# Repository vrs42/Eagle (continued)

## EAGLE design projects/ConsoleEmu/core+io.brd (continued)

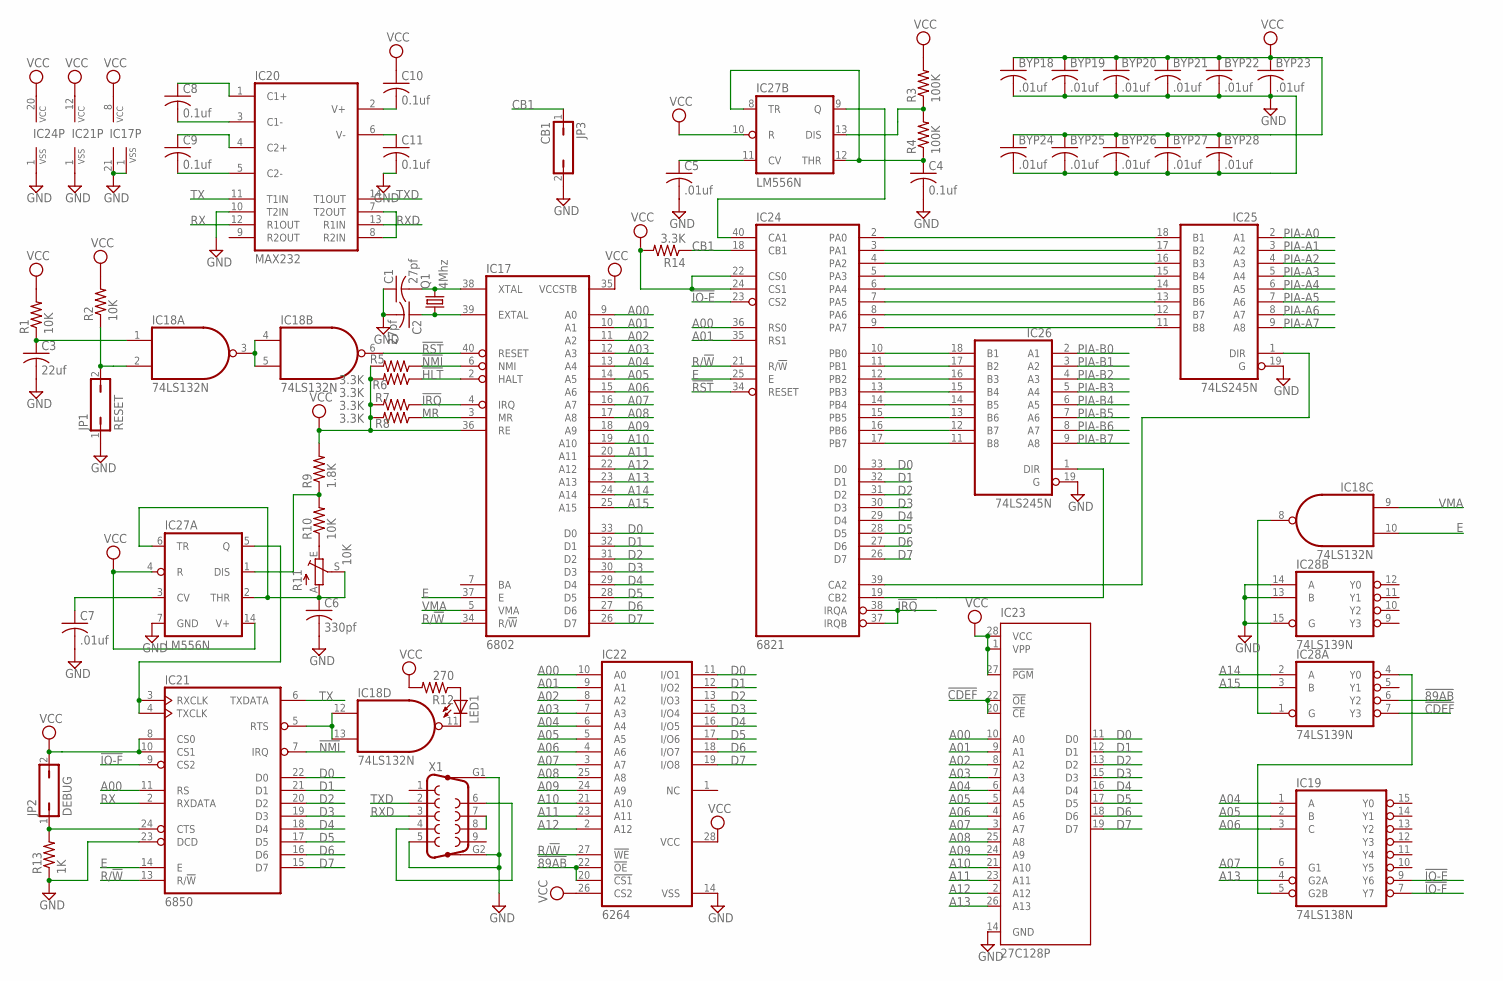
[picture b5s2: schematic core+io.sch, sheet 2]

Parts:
BYP18, BYP19, BYP20, BYP21, BYP22, BYP23, BYP24, BYP25, BYP26, BYP27, BYP28: .01uf; C050-025X075
C1, C2: 27pf; C050-025X075
C3: 22uf; C102-043X133
C4, C8, C9, C10, C11: 0.1uf; C050-025X075
C5, C7: .01uf; C050-025X075
C6: 330pf; C050-025X075
IC17: 6802; DIL40
IC18: 74LS132N; DIL14
IC19: 74LS138N; DIL16
IC20: MAX232; DIL16
IC21: 6850; DIL24
IC22: 6264; DIL28-6
IC23: 27C128P; DIL28-6
IC24: 6821; DIL40
IC25, IC26: 74LS245N; DIL20
IC27: LM556N; DIL14
IC28: 74LS139N; DIL16
JP1: RESET; JP1
JP2: DEBUG; JP1
JP3: CB1; JP1
LED1: LED3MM
Q1: 4Mhz; HC18U-V
R1, R2, R10: 10K; 0207/7
R3, R4: 100K; 0207/7
R5, R6, R7, R8, R14: 3.3K; 0207/7
R9: 1.8K; 0207/7
R11: 10K; SP19L
R12: 270; 0207/7
R13: 1K; 0207/7
X1: F09HP

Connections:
!89AB: IC22.20 (!CS1), IC22.22 (!OE), IC28.6 (Y2)
!CDEF: IC23.20 (!CE), IC23.22 (!OE), IC28.7 (Y3)
!HLT: IC17.2 (HALT), R5.1
!IO-E: IC19.9 (Y6), IC24.23 (CS2)
!IO-F: IC19.7 (Y7), IC21.9 (CS2)
!IRQ: IC17.4 (IRQ), IC24.37 (IRQB), IC24.38 (IRQA), R7.1
!NMI: IC17.6 (NMI), IC21.7 (IRQ), R6.1
!RST: IC17.40 (RESET), IC18.6 (O), IC24.34 (RESET)
A00: IC17.9 (A0), IC21.11 (RS), IC22.10 (A0), IC23.10 (A0), IC24.36 (RS0)
A01: IC17.10 (A1), IC22.9 (A1), IC23.9 (A1), IC24.35 (RS1)
A02: IC17.11 (A2), IC22.8 (A2), IC23.8 (A2)
A03: IC17.12 (A3), IC22.7 (A3), IC23.7 (A3)
A04: IC17.13 (A4), IC19.1 (A), IC22.6 (A4), IC23.6 (A4)
A05: IC17.14 (A5), IC19.2 (B), IC22.5 (A5), IC23.5 (A5)
A06: IC17.15 (A6), IC19.3 (C), IC22.4 (A6), IC23.4 (A6)
A07: IC17.16 (A7), IC19.6 (G1), IC22.3 (A7), IC23.3 (A7)
A08: IC17.17 (A8), IC22.25 (A8), IC23.25 (A8)
A09: IC17.18 (A9), IC22.24 (A9), IC23.24 (A9)
A10: IC17.19 (A10), IC22.21 (A10), IC23.21 (A10)
A11: IC17.20 (A11), IC22.23 (A11), IC23.23 (A11)
A12: IC17.22 (A12), IC22.2 (A12), IC23.2 (A12)
A13: IC17.23 (A13), IC19.4 (G2A), IC23.26 (A13)
A14: IC17.24 (A14), IC28.2 (A)
A15: IC17.25 (A15), IC28.3 (B)
CB1: IC24.18 (CB1), JP3.1, R14.1
D0: IC17.33 (D0), IC21.22 (D0), IC22.11 (I/O1), IC23.11 (D0), IC24.33 (D0)
D1: IC17.32 (D1), IC21.21 (D1), IC22.12 (I/O2), IC23.12 (D1), IC24.32 (D1)
D2: IC17.31 (D2), IC21.20 (D2), IC22.13 (I/O3), IC23.13 (D2), IC24.31 (D2)
D3: IC17.30 (D3), IC21.19 (D3), IC22.15 (I/O4), IC23.15 (D3), IC24.30 (D3)
D4: IC17.29 (D4), IC21.18 (D4), IC22.16 (I/O5), IC23.16 (D4), IC24.29 (D4)
D5: IC17.28 (D5), IC21.17 (D5), IC22.17 (I/O6), IC23.17 (D5), IC24.28 (D5)
D6: IC17.27 (D6), IC21.16 (D6), IC22.18 (I/O7), IC23.18 (D6), IC24.27 (D6)
D7: IC17.26 (D7), IC21.15 (D7), IC22.19 (I/O8), IC23.19 (D7), IC24.26 (D7)
E: IC17.37 (E), IC18.10 (I1), IC21.14 (E), IC24.25 (E)
GND: BYP18.2, BYP19.2, BYP20.2, BYP21.2, BYP22.2, BYP23.2, BYP24.2, BYP25.2, BYP26.2, BYP27.2, BYP28.2, C1.1, C2.2, C3.2, C4.2, C5.2, C6.2, C7.2, C11.2, IC17.1 (VSS), IC17.21 (VSS), IC18.7 (GND), IC19.8 (GND), IC20.10 (T2IN), IC20.15 (GND), IC21.1 (VSS), IC21.23 (DCD), IC22.14 (VSS), IC23.14 (GND), IC24.1 (VSS), IC25.10 (GND), IC25.19 (G), IC26.10 (GND), IC26.19 (G), IC27.7 (GND), IC28.8 (GND), IC28.13 (B), IC28.14 (A), IC28.15 (G), JP1.1, JP3.2, R13.1, X1.5, X1.G1, X1.G2; also elsewhere on the board
MR: IC17.3 (MR), R8.1
unnamed: C2.1, IC17.39 (EXTAL), Q1.1
unnamed: C1.2, IC17.38 (XTAL), Q1.2
unnamed: IC24.2 (PA0), IC25.18 (B1)
unnamed: IC18.3 (O), IC18.4 (I0), IC18.5 (I1)
unnamed: C3.1, IC18.1 (I0), R1.1
unnamed: IC18.2 (I1), JP1.2, R2.1
unnamed: IC21.3 (RXCLK), IC21.4 (TXCLK), IC27.5 (Q)
unnamed: IC24.10 (PB0), IC26.18 (B1)
unnamed: IC24.11 (PB1), IC26.17 (B2)
unnamed: C6.1, IC27.2 (THR), IC27.6 (TR), R11.A, R11.S
unnamed: IC27.1 (DIS), R9.1, R10.2
unnamed: IC24.12 (PB2), IC26.16 (B3)
unnamed: IC24.13 (PB3), IC26.15 (B4)
unnamed: IC24.14 (PB4), IC26.14 (B5)
unnamed: IC24.15 (PB5), IC26.13 (B6)
unnamed: IC24.16 (PB6), IC26.12 (B7)
unnamed: IC24.17 (PB7), IC26.11 (B8)
unnamed: IC24.3 (PA1), IC25.17 (B2)
unnamed: IC24.4 (PA2), IC25.16 (B3)
unnamed: IC24.5 (PA3), IC25.15 (B4)
unnamed: IC24.6 (PA4), IC25.14 (B5)
unnamed: IC24.7 (PA5), IC25.13 (B6)
unnamed: IC24.8 (PA6), IC25.12 (B7)
unnamed: IC24.9 (PA7), IC25.11 (B8)
unnamed: IC24.19 (CB2), IC26.1 (DIR)
unnamed: IC24.39 (CA2), IC25.1 (DIR)
unnamed: IC24.40 (CA1), IC27.9 (Q)
unnamed: C4.1, IC27.8 (TR), IC27.12 (THR), R4.1
unnamed: IC27.13 (DIS), R3.1, R4.2
unnamed: C5.1, IC27.11 (CV)
unnamed: R10.1, R11.E
unnamed: X1.4, X1.6
unnamed: X1.7, X1.8
unnamed: IC18.12 (I0), IC18.13 (I1), IC21.5 (RTS)
unnamed: IC18.11 (O), LED1.K (C)
unnamed: LED1.A, R12.1
unnamed: IC21.24 (CTS), JP2.1, R13.2
unnamed: IC18.8 (O), IC28.1 (G)
unnamed: IC19.5 (G2B), IC28.4 (Y0)
unnamed: IC20.7 (T2OUT), IC20.8 (R2IN)
unnamed: C7.1, IC27.3 (CV)
unnamed: C9.2, IC20.5 (C2-)
unnamed: C9.1, IC20.4 (C2+)
unnamed: C8.2, IC20.3 (C1-)
unnamed: C8.1, IC20.1 (C1+)
unnamed: C11.1, IC20.6 (V-)
unnamed: C10.2, IC20.2 (V+)
PIA-A0: IC25.2 (A1); also elsewhere on the board
PIA-A1: IC25.3 (A2); also elsewhere on the board
PIA-A2: IC25.4 (A3); also elsewhere on the board
PIA-A3: IC25.5 (A4); also elsewhere on the board
PIA-A4: IC25.6 (A5); also elsewhere on the board
PIA-A5: IC25.7 (A6); also elsewhere on the board
PIA-A6: IC25.8 (A7); also elsewhere on the board
PIA-A7: IC25.9 (A8); also elsewhere on the board
PIA-B0: IC26.2 (A1); also elsewhere on the board
PIA-B1: IC26.3 (A2); also elsewhere on the board
PIA-B2: IC26.4 (A3); also elsewhere on the board
PIA-B3: IC26.5 (A4); also elsewhere on the board
PIA-B4: IC26.6 (A5); also elsewhere on the board
PIA-B5: IC26.7 (A6); also elsewhere on the board
PIA-B6: IC26.8 (A7); also elsewhere on the board
PIA-B7: IC26.9 (A8); also elsewhere on the board
R/!W: IC17.34 (R/!W), IC21.13 (R/!W), IC22.27 (!WE), IC24.21 (R/!W)
RX: IC20.12 (R1OUT), IC21.2 (RXDATA)
RXD: IC20.13 (R1IN), X1.3
TX: IC20.11 (T1IN), IC21.6 (TXDATA)
TXD: IC20.14 (T1OUT), X1.2
VCC: BYP18.1, BYP19.1, BYP20.1, BYP21.1, BYP22.1, BYP23.1, BYP24.1, BYP25.1, BYP26.1, BYP27.1, BYP28.1, C10.1, IC17.8 (VCC), IC17.35 (VCCSTB), IC17.36 (RE), IC18.14 (VCC), IC19.16 (VCC), IC20.16 (VCC), IC21.8 (CS0), IC21.10 (CS1), IC21.12 (VCC), IC22.26 (CS2), IC22.28 (VCC), IC23.1 (VPP), IC23.27 (!PGM), IC23.28 (VCC), IC24.20 (VCC), IC24.22 (CS0), IC24.24 (CS1), IC25.20 (VCC), IC26.20 (VCC), IC27.4 (R), IC27.10 (R), IC27.14 (V+), IC28.16 (VCC), JP2.2, R1.2, R2.2, R3.2, R5.2, R6.2, R7.2, R8.2, R9.2, R12.2, R14.2; also elsewhere on the board
VMA: IC17.5 (VMA), IC18.9 (I0)

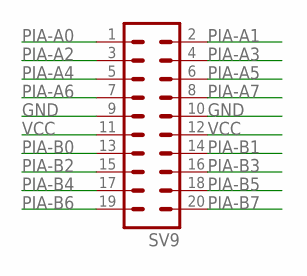
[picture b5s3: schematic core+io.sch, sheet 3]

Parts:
SV9: MA10-2

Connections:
GND: SV9.9, SV9.10; also elsewhere on the board
PIA-A0: SV9.1; also elsewhere on the board
PIA-A1: SV9.2; also elsewhere on the board
PIA-A2: SV9.3; also elsewhere on the board
PIA-A3: SV9.4; also elsewhere on the board
PIA-A4: SV9.5; also elsewhere on the board
PIA-A5: SV9.6; also elsewhere on the board
PIA-A6: SV9.7; also elsewhere on the board
PIA-A7: SV9.8; also elsewhere on the board
PIA-B0: SV9.13; also elsewhere on the board
PIA-B1: SV9.14; also elsewhere on the board
PIA-B2: SV9.15; also elsewhere on the board
PIA-B3: SV9.16; also elsewhere on the board
PIA-B4: SV9.17; also elsewhere on the board
PIA-B5: SV9.18; also elsewhere on the board
PIA-B6: SV9.19; also elsewhere on the board
PIA-B7: SV9.20; also elsewhere on the board
VCC: SV9.11, SV9.12; also elsewhere on the board

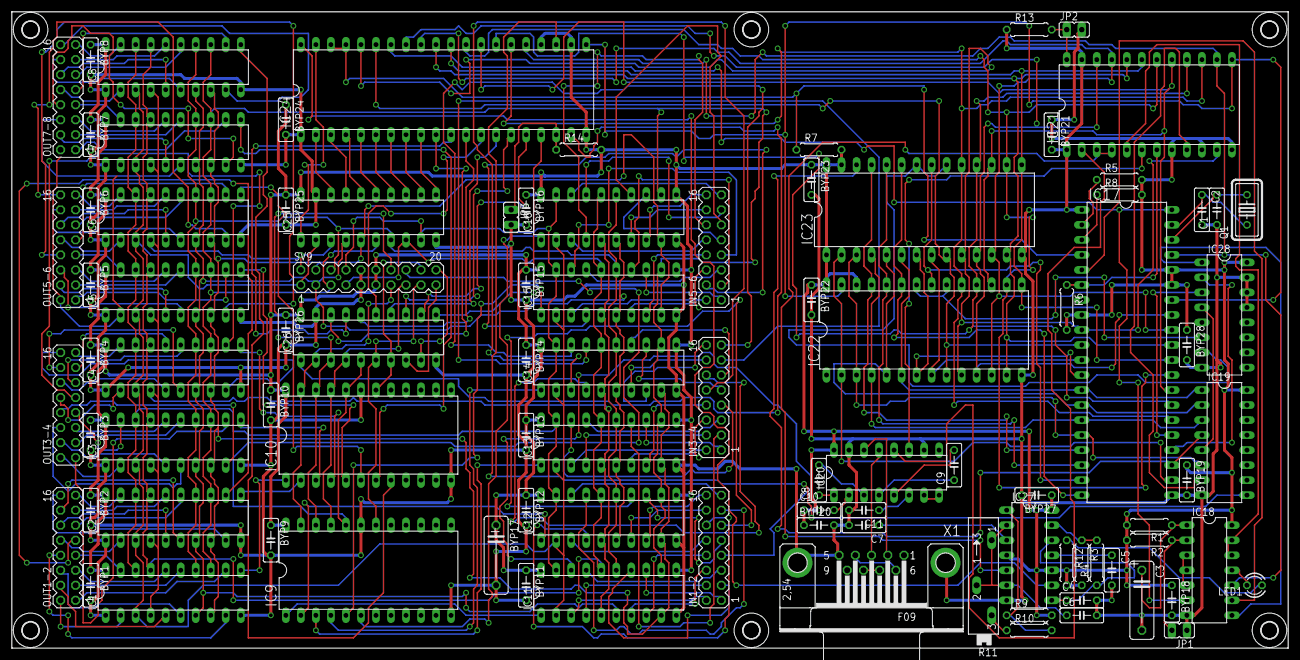
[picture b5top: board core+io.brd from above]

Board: 2 copper layers, 215.9 x 107.6 mm, 101 parts (0 on the bottom side), 232 nets.

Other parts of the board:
U$1, U$2, U$3, U$4, U$5, U$6: 2,8

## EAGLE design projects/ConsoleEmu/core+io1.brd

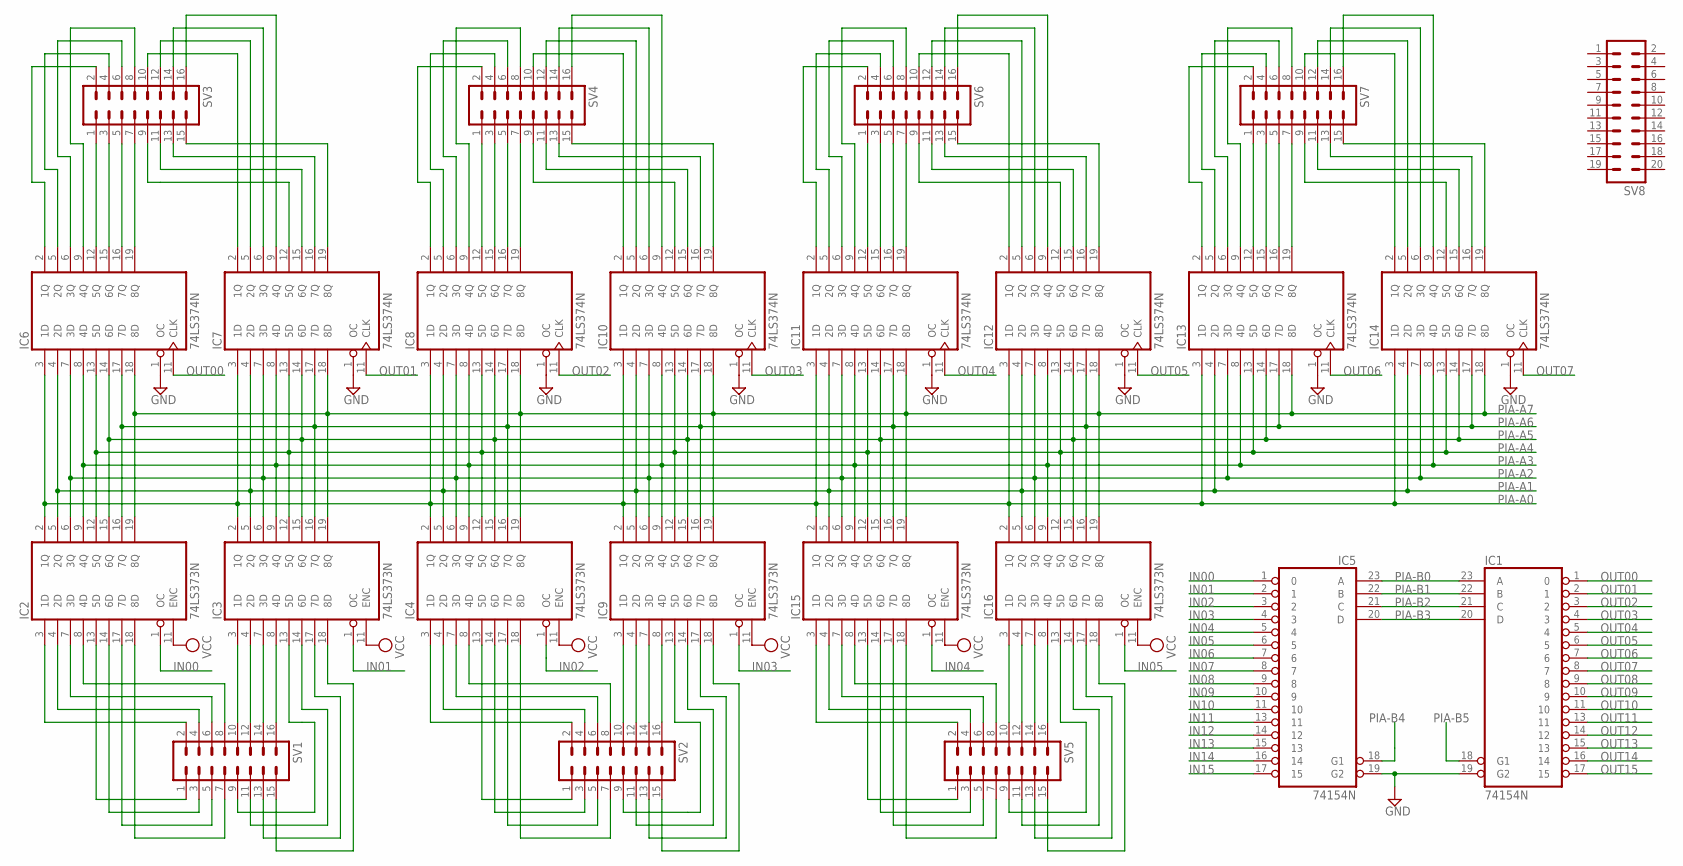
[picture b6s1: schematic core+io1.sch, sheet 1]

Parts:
IC1, IC5: 74154N; DIL24-6
IC2, IC3, IC4, IC9, IC15, IC16: 74LS373N; DIL20
IC6, IC7, IC8, IC10, IC11, IC12, IC13, IC14: 74LS374N; DIL20
SV1, SV2, SV3, SV4, SV5, SV6, SV7: MA08-2
SV8: MA10-2W

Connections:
GND: IC1.12 (GND), IC1.19 (G2), IC2.10 (GND), IC3.10 (GND), IC4.10 (GND), IC5.12 (GND), IC5.19 (G2), IC6.1 (OC), IC6.10 (GND), IC7.1 (OC), IC7.10 (GND), IC8.1 (OC), IC8.10 (GND), IC9.10 (GND), IC10.1 (OC), IC10.10 (GND), IC11.1 (OC), IC11.10 (GND), IC12.1 (OC), IC12.10 (GND), IC13.1 (OC), IC13.10 (GND), IC14.1 (OC), IC14.10 (GND), IC15.10 (GND), IC16.10 (GND); also elsewhere on the board
IN00: IC2.1 (OC), IC5.1 (0)
IN01: IC3.1 (OC), IC5.2 (1)
IN02: IC4.1 (OC), IC5.3 (2)
IN03: IC5.4 (3), IC9.1 (OC)
IN04: IC5.5 (4), IC15.1 (OC)
IN05: IC5.6 (5), IC16.1 (OC)
IN06: IC5.7 (6)
IN07: IC5.8 (7)
IN08: IC5.9 (8)
IN09: IC5.10 (9)
IN10: IC5.11 (10)
IN11: IC5.13 (11)
IN12: IC5.14 (12)
IN13: IC5.15 (13)
IN14: IC5.16 (14)
IN15: IC5.17 (15)
unnamed: IC3.3 (1D), SV1.10
unnamed: IC3.4 (2D), SV1.12
unnamed: IC3.7 (3D), SV1.14
unnamed: IC3.8 (4D), SV1.16
unnamed: IC2.8 (4D), SV1.8
unnamed: IC2.7 (3D), SV1.6
unnamed: IC2.4 (2D), SV1.4
unnamed: IC2.3 (1D), SV1.2
unnamed: IC2.13 (5D), SV1.1
unnamed: IC2.14 (6D), SV1.3
unnamed: IC2.17 (7D), SV1.5
unnamed: IC2.18 (8D), SV1.7
unnamed: IC3.13 (5D), SV1.9
unnamed: IC3.14 (6D), SV1.11
unnamed: IC3.17 (7D), SV1.13
unnamed: IC3.18 (8D), SV1.15
unnamed: IC11.2 (1Q), SV6.2
unnamed: IC9.3 (1D), SV2.10
unnamed: IC9.4 (2D), SV2.12
unnamed: IC9.7 (3D), SV2.14
unnamed: IC9.8 (4D), SV2.16
unnamed: IC8.12 (5Q), SV4.1
unnamed: IC8.15 (6Q), SV4.3
unnamed: IC8.16 (7Q), SV4.5
unnamed: IC8.19 (8Q), SV4.7
unnamed: IC4.3 (1D), SV2.2
unnamed: IC4.4 (2D), SV2.4
unnamed: IC4.7 (3D), SV2.6
unnamed: IC4.8 (4D), SV2.8
unnamed: IC9.13 (5D), SV2.9
unnamed: IC9.14 (6D), SV2.11
unnamed: IC9.17 (7D), SV2.13
unnamed: IC9.18 (8D), SV2.15
unnamed: IC4.13 (5D), SV2.1
unnamed: IC4.14 (6D), SV2.3
unnamed: IC4.17 (7D), SV2.5
unnamed: IC4.18 (8D), SV2.7
unnamed: IC8.5 (2Q), SV4.4
unnamed: IC8.6 (3Q), SV4.6
unnamed: IC8.2 (1Q), SV4.2
unnamed: IC8.9 (4Q), SV4.8
unnamed: IC6.12 (5Q), SV3.1
unnamed: IC6.15 (6Q), SV3.3
unnamed: IC6.16 (7Q), SV3.5
unnamed: IC6.19 (8Q), SV3.7
unnamed: IC6.2 (1Q), SV3.2
unnamed: IC6.5 (2Q), SV3.4
unnamed: IC6.6 (3Q), SV3.6
unnamed: IC6.9 (4Q), SV3.8
unnamed: IC7.19 (8Q), SV3.15
unnamed: IC7.16 (7Q), SV3.13
unnamed: IC7.15 (6Q), SV3.11
unnamed: IC7.12 (5Q), SV3.9
unnamed: IC7.2 (1Q), SV3.10
unnamed: IC7.5 (2Q), SV3.12
unnamed: IC7.6 (3Q), SV3.14
unnamed: IC7.9 (4Q), SV3.16
unnamed: IC10.2 (1Q), SV4.10
unnamed: IC10.5 (2Q), SV4.12
unnamed: IC10.6 (3Q), SV4.14
unnamed: IC10.9 (4Q), SV4.16
unnamed: IC10.19 (8Q), SV4.15
unnamed: IC10.16 (7Q), SV4.13
unnamed: IC10.15 (6Q), SV4.11
unnamed: IC10.12 (5Q), SV4.9
unnamed: IC16.3 (1D), SV5.10
unnamed: IC16.4 (2D), SV5.12
unnamed: IC16.7 (3D), SV5.14
unnamed: IC16.8 (4D), SV5.16
unnamed: IC11.12 (5Q), SV6.1
unnamed: IC11.15 (6Q), SV6.3
unnamed: IC11.16 (7Q), SV6.5
unnamed: IC11.19 (8Q), SV6.7
unnamed: IC13.12 (5Q), SV7.1
unnamed: IC13.15 (6Q), SV7.3
unnamed: IC13.16 (7Q), SV7.5
unnamed: IC13.19 (8Q), SV7.7
unnamed: IC11.5 (2Q), SV6.4
unnamed: IC11.6 (3Q), SV6.6
unnamed: IC11.9 (4Q), SV6.8
unnamed: IC12.12 (5Q), SV6.9
unnamed: IC12.15 (6Q), SV6.11
unnamed: IC12.16 (7Q), SV6.13
unnamed: IC12.19 (8Q), SV6.15
unnamed: IC12.2 (1Q), SV6.10
unnamed: IC12.5 (2Q), SV6.12
unnamed: IC12.6 (3Q), SV6.14
unnamed: IC12.9 (4Q), SV6.16
unnamed: IC15.3 (1D), SV5.2
unnamed: IC15.4 (2D), SV5.4
unnamed: IC15.7 (3D), SV5.6
unnamed: IC15.8 (4D), SV5.8
unnamed: IC16.13 (5D), SV5.9
unnamed: IC16.14 (6D), SV5.11
unnamed: IC16.17 (7D), SV5.13
unnamed: IC16.18 (8D), SV5.15
unnamed: IC15.13 (5D), SV5.1
unnamed: IC15.14 (6D), SV5.3
unnamed: IC15.17 (7D), SV5.5
unnamed: IC15.18 (8D), SV5.7
unnamed: IC14.19 (8Q), SV7.15
unnamed: IC14.16 (7Q), SV7.13
unnamed: IC14.15 (6Q), SV7.11
unnamed: IC14.12 (5Q), SV7.9
unnamed: IC14.2 (1Q), SV7.10
unnamed: IC14.5 (2Q), SV7.12
unnamed: IC14.6 (3Q), SV7.14
unnamed: IC14.9 (4Q), SV7.16
unnamed: IC13.9 (4Q), SV7.8
unnamed: IC13.6 (3Q), SV7.6
unnamed: IC13.5 (2Q), SV7.4
unnamed: IC13.2 (1Q), SV7.2
OUT00: IC1.1 (0), IC6.11 (CLK)
OUT01: IC1.2 (1), IC7.11 (CLK)
OUT02: IC1.3 (2), IC8.11 (CLK)
OUT03: IC1.4 (3), IC10.11 (CLK)
OUT04: IC1.5 (4), IC11.11 (CLK)
OUT05: IC1.6 (5), IC12.11 (CLK)
OUT06: IC1.7 (6), IC13.11 (CLK)
OUT07: IC1.8 (7), IC14.11 (CLK)
OUT08: IC1.9 (8)
OUT09: IC1.10 (9)
OUT10: IC1.11 (10)
OUT11: IC1.13 (11)
OUT12: IC1.14 (12)
OUT13: IC1.15 (13)
OUT14: IC1.16 (14)
OUT15: IC1.17 (15)
PIA-A0: IC2.2 (1Q), IC3.2 (1Q), IC4.2 (1Q), IC6.3 (1D), IC7.3 (1D), IC8.3 (1D), IC9.2 (1Q), IC10.3 (1D), IC11.3 (1D), IC12.3 (1D), IC13.3 (1D), IC14.3 (1D), IC15.2 (1Q), IC16.2 (1Q); also elsewhere on the board
PIA-A1: IC2.5 (2Q), IC3.5 (2Q), IC4.5 (2Q), IC6.4 (2D), IC7.4 (2D), IC8.4 (2D), IC9.5 (2Q), IC10.4 (2D), IC11.4 (2D), IC12.4 (2D), IC13.4 (2D), IC14.4 (2D), IC15.5 (2Q), IC16.5 (2Q); also elsewhere on the board
PIA-A2: IC2.6 (3Q), IC3.6 (3Q), IC4.6 (3Q), IC6.7 (3D), IC7.7 (3D), IC8.7 (3D), IC9.6 (3Q), IC10.7 (3D), IC11.7 (3D), IC12.7 (3D), IC13.7 (3D), IC14.7 (3D), IC15.6 (3Q), IC16.6 (3Q); also elsewhere on the board
PIA-A3: IC2.9 (4Q), IC3.9 (4Q), IC4.9 (4Q), IC6.8 (4D), IC7.8 (4D), IC8.8 (4D), IC9.9 (4Q), IC10.8 (4D), IC11.8 (4D), IC12.8 (4D), IC13.8 (4D), IC14.8 (4D), IC15.9 (4Q), IC16.9 (4Q); also elsewhere on the board
PIA-A4: IC2.12 (5Q), IC3.12 (5Q), IC4.12 (5Q), IC6.13 (5D), IC7.13 (5D), IC8.13 (5D), IC9.12 (5Q), IC10.13 (5D), IC11.13 (5D), IC12.13 (5D), IC13.13 (5D), IC14.13 (5D), IC15.12 (5Q), IC16.12 (5Q); also elsewhere on the board
PIA-A5: IC2.15 (6Q), IC3.15 (6Q), IC4.15 (6Q), IC6.14 (6D), IC7.14 (6D), IC8.14 (6D), IC9.15 (6Q), IC10.14 (6D), IC11.14 (6D), IC12.14 (6D), IC13.14 (6D), IC14.14 (6D), IC15.15 (6Q), IC16.15 (6Q); also elsewhere on the board
PIA-A6: IC2.16 (7Q), IC3.16 (7Q), IC4.16 (7Q), IC6.17 (7D), IC7.17 (7D), IC8.17 (7D), IC9.16 (7Q), IC10.17 (7D), IC11.17 (7D), IC12.17 (7D), IC13.17 (7D), IC14.17 (7D), IC15.16 (7Q), IC16.16 (7Q); also elsewhere on the board
PIA-A7: IC2.19 (8Q), IC3.19 (8Q), IC4.19 (8Q), IC6.18 (8D), IC7.18 (8D), IC8.18 (8D), IC9.19 (8Q), IC10.18 (8D), IC11.18 (8D), IC12.18 (8D), IC13.18 (8D), IC14.18 (8D), IC15.19 (8Q), IC16.19 (8Q); also elsewhere on the board
PIA-B0: IC1.23 (A), IC5.23 (A); also elsewhere on the board
PIA-B1: IC1.22 (B), IC5.22 (B); also elsewhere on the board
PIA-B2: IC1.21 (C), IC5.21 (C); also elsewhere on the board
PIA-B3: IC1.20 (D), IC5.20 (D); also elsewhere on the board
PIA-B4: IC5.18 (G1); also elsewhere on the board
PIA-B5: IC1.18 (G1); also elsewhere on the board
VCC: IC1.24 (VCC), IC2.11 (ENC), IC2.20 (VCC), IC3.11 (ENC), IC3.20 (VCC), IC4.11 (ENC), IC4.20 (VCC), IC5.24 (VCC), IC6.20 (VCC), IC7.20 (VCC), IC8.20 (VCC), IC9.11 (ENC), IC9.20 (VCC), IC10.20 (VCC), IC11.20 (VCC), IC12.20 (VCC), IC13.20 (VCC), IC14.20 (VCC), IC15.11 (ENC), IC15.20 (VCC), IC16.11 (ENC), IC16.20 (VCC); also elsewhere on the board

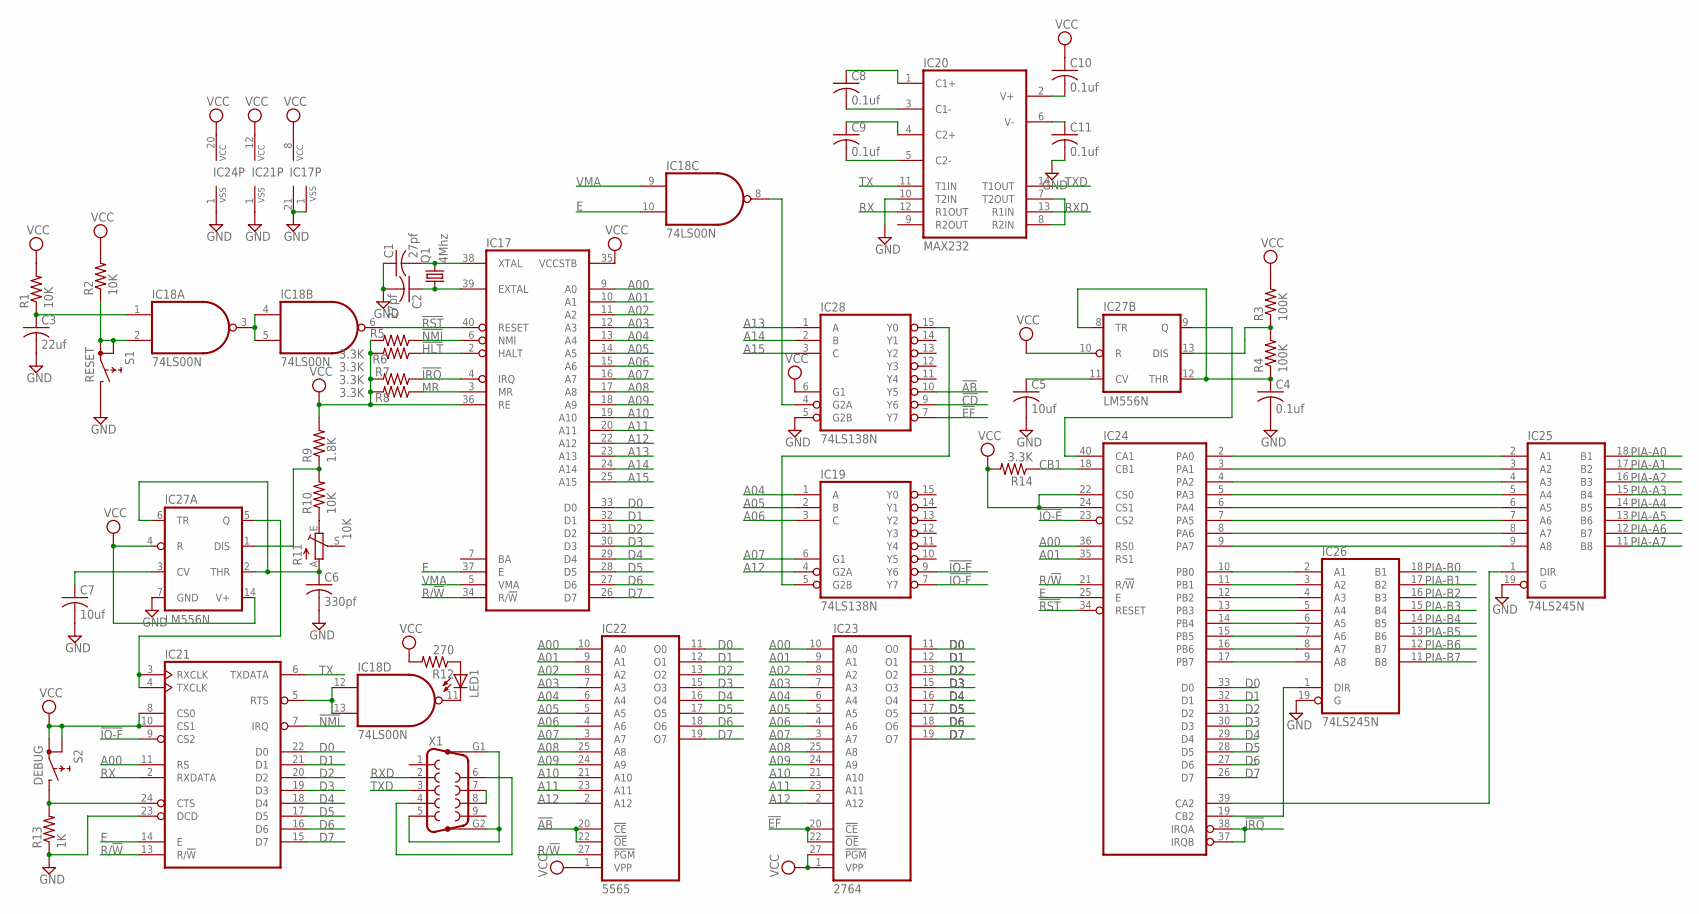
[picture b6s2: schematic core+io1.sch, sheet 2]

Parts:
C1, C2: 27pf; C050-025X075
C3: 22uf; C050-025X075
C4, C8, C9, C10, C11: 0.1uf; C050-025X075
C5, C7: 10uf; C050-025X075
C6: 330pf; C050-025X075
IC17: 6802; DIL40
IC18: 74LS00N; DIL14
IC19, IC28: 74LS138N; DIL16
IC20: MAX232; DIL16
IC21: 6850; DIL24
IC22: 5565; DIL28
IC23: 2764; DIL28
IC24: 6821; DIL40
IC25, IC26: 74LS245N; DIL20
IC27: LM556N; DIL14
LED1: LED3MM
Q1: 4Mhz; HC18U-V
R1, R2, R10: 10K; 0207/7
R3, R4: 100K; 0207/7
R5, R6, R7, R8, R14: 3.3K; 0207/7
R9: 1.8K; 0207/7
R11: 10K; SP19L
R12: 270; 0207/7
R13: 1K; 0207/7
S1: RESET; RDT1034
S2: DEBUG; RDT1034
X1: F09HP

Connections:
!AB: IC22.20 (!CE), IC22.22 (!OE), IC28.10 (Y5)
!CD: IC28.9 (Y6)
!EF: IC23.20 (!CE), IC23.22 (!OE), IC28.7 (Y7)
!HLT: IC17.2 (HALT), R5.1
!IO-E: IC19.9 (Y6), IC24.23 (CS2)
!IO-F: IC19.7 (Y7), IC21.9 (CS2)
!IRQ: IC17.4 (IRQ), IC24.37 (IRQB), IC24.38 (IRQA), R7.1
!NMI: IC17.6 (NMI), IC21.7 (IRQ), R6.1
!RST: IC17.40 (RESET), IC18.6 (O), IC24.34 (RESET)
A00: IC17.9 (A0), IC21.11 (RS), IC22.10 (A0), IC23.10 (A0), IC24.36 (RS0)
A01: IC17.10 (A1), IC22.9 (A1), IC23.9 (A1), IC24.35 (RS1)
A02: IC17.11 (A2), IC22.8 (A2), IC23.8 (A2)
A03: IC17.12 (A3), IC22.7 (A3), IC23.7 (A3)
A04: IC17.13 (A4), IC19.1 (A), IC22.6 (A4), IC23.6 (A4)
A05: IC17.14 (A5), IC19.2 (B), IC22.5 (A5), IC23.5 (A5)
A06: IC17.15 (A6), IC19.3 (C), IC22.4 (A6), IC23.4 (A6)
A07: IC17.16 (A7), IC19.6 (G1), IC22.3 (A7), IC23.3 (A7)
A08: IC17.17 (A8), IC22.25 (A8), IC23.25 (A8)
A09: IC17.18 (A9), IC22.24 (A9), IC23.24 (A9)
A10: IC17.19 (A10), IC22.21 (A10), IC23.21 (A10)
A11: IC17.20 (A11), IC22.23 (A11), IC23.23 (A11)
A12: IC17.22 (A12), IC19.4 (G2A), IC22.2 (A12), IC23.2 (A12)
A13: IC17.23 (A13), IC28.1 (A)
A14: IC17.24 (A14), IC28.2 (B)
A15: IC17.25 (A15), IC28.3 (C)
CB1: IC24.18 (CB1), R14.1
D0: IC17.33 (D0), IC21.22 (D0), IC22.11 (O0), IC23.11 (O0), IC24.33 (D0)
D1: IC17.32 (D1), IC21.21 (D1), IC22.12 (O1), IC23.12 (O1), IC24.32 (D1)
D2: IC17.31 (D2), IC21.20 (D2), IC22.13 (O2), IC23.13 (O2), IC24.31 (D2)
D3: IC17.30 (D3), IC21.19 (D3), IC22.15 (O3), IC23.15 (O3), IC24.30 (D3)
D4: IC17.29 (D4), IC21.18 (D4), IC22.16 (O4), IC23.16 (O4), IC24.29 (D4)
D5: IC17.28 (D5), IC21.17 (D5), IC22.17 (O5), IC23.17 (O5), IC24.28 (D5)
D6: IC17.27 (D6), IC21.16 (D6), IC22.18 (O6), IC23.18 (O6), IC24.27 (D6)
D7: IC17.26 (D7), IC21.15 (D7), IC22.19 (O7), IC23.19 (O7), IC24.26 (D7)
E: IC17.37 (E), IC18.10 (I1), IC21.14 (E), IC24.25 (E)
GND: C1.1, C2.2, C3.2, C4.2, C5.2, C6.2, C7.2, C11.2, IC17.1 (VSS), IC17.21 (VSS), IC18.7 (GND), IC19.8 (GND), IC20.10 (T2IN), IC20.15 (GND), IC21.1 (VSS), IC21.23 (DCD), IC22.14 (GND), IC23.14 (GND), IC24.1 (VSS), IC25.10 (GND), IC25.19 (G), IC26.10 (GND), IC26.19 (G), IC27.7 (GND), IC28.5 (G2B), IC28.8 (GND), R13.1, S1.B; also elsewhere on the board
MR: IC17.3 (MR), R8.1
unnamed: C2.1, IC17.39 (EXTAL), Q1.1
unnamed: C1.2, IC17.38 (XTAL), Q1.2
unnamed: IC24.2 (PA0), IC25.2 (A1)
unnamed: IC18.3 (O), IC18.4 (I0), IC18.5 (I1)
unnamed: C3.1, IC18.1 (I0), R1.1
unnamed: IC18.2 (I1), R2.1, S1.A, S1.A1
unnamed: IC21.3 (RXCLK), IC21.4 (TXCLK), IC27.5 (Q)
unnamed: IC24.10 (PB0), IC26.2 (A1)
unnamed: IC24.11 (PB1), IC26.3 (A2)
unnamed: C6.1, IC27.2 (THR), IC27.6 (TR), R11.A
unnamed: IC27.1 (DIS), R9.1, R10.2
unnamed: IC24.12 (PB2), IC26.4 (A3)
unnamed: IC24.13 (PB3), IC26.5 (A4)
unnamed: IC24.14 (PB4), IC26.6 (A5)
unnamed: IC24.15 (PB5), IC26.7 (A6)
unnamed: IC24.16 (PB6), IC26.8 (A7)
unnamed: IC24.17 (PB7), IC26.9 (A8)
unnamed: IC24.3 (PA1), IC25.3 (A2)
unnamed: IC24.4 (PA2), IC25.4 (A3)
unnamed: IC24.5 (PA3), IC25.5 (A4)
unnamed: IC24.6 (PA4), IC25.6 (A5)
unnamed: IC24.7 (PA5), IC25.7 (A6)
unnamed: IC24.8 (PA6), IC25.8 (A7)
unnamed: IC24.9 (PA7), IC25.9 (A8)
unnamed: IC24.19 (CB2), IC26.1 (DIR)
unnamed: IC24.39 (CA2), IC25.1 (DIR)
unnamed: IC24.40 (CA1), IC27.9 (Q)
unnamed: C4.1, IC27.8 (TR), IC27.12 (THR), R4.1
unnamed: IC27.13 (DIS), R3.1, R4.2
unnamed: C5.1, IC27.11 (CV)
unnamed: R10.1, R11.E
unnamed: X1.4, X1.6
unnamed: X1.7, X1.8
unnamed: X1.5, X1.G1, X1.G2
unnamed: IC18.12 (I0), IC18.13 (I1), IC21.5 (RTS)
unnamed: IC18.11 (O), LED1.K (C)
unnamed: LED1.A, R12.1
unnamed: IC21.24 (CTS), R13.2, S2.B
unnamed: IC18.8 (O), IC28.4 (G2A)
unnamed: IC19.5 (G2B), IC28.15 (Y0)
unnamed: IC20.7 (T2OUT), IC20.8 (R2IN)
unnamed: C7.1, IC27.3 (CV)
unnamed: C9.2, IC20.5 (C2-)
unnamed: C9.1, IC20.4 (C2+)
unnamed: C8.2, IC20.3 (C1-)
unnamed: C8.1, IC20.1 (C1+)
unnamed: C11.1, IC20.6 (V-)
unnamed: C10.2, IC20.2 (V+)
PIA-A0: IC25.18 (B1); also elsewhere on the board
PIA-A1: IC25.17 (B2); also elsewhere on the board
PIA-A2: IC25.16 (B3); also elsewhere on the board
PIA-A3: IC25.15 (B4); also elsewhere on the board
PIA-A4: IC25.14 (B5); also elsewhere on the board
PIA-A5: IC25.13 (B6); also elsewhere on the board
PIA-A6: IC25.12 (B7); also elsewhere on the board
PIA-A7: IC25.11 (B8); also elsewhere on the board
PIA-B0: IC26.18 (B1); also elsewhere on the board
PIA-B1: IC26.17 (B2); also elsewhere on the board
PIA-B2: IC26.16 (B3); also elsewhere on the board
PIA-B3: IC26.15 (B4); also elsewhere on the board
PIA-B4: IC26.14 (B5); also elsewhere on the board
PIA-B5: IC26.13 (B6); also elsewhere on the board
PIA-B6: IC26.12 (B7)
PIA-B7: IC26.11 (B8)
R/!W: IC17.34 (R/!W), IC21.13 (R/!W), IC22.27 (!PGM), IC24.21 (R/!W)
RX: IC20.12 (R1OUT), IC21.2 (RXDATA)
RXD: IC20.13 (R1IN), X1.2
TX: IC20.11 (T1IN), IC21.6 (TXDATA)
TXD: IC20.14 (T1OUT), X1.3
VCC: C10.1, IC17.8 (VCC), IC17.35 (VCCSTB), IC17.36 (RE), IC18.14 (VCC), IC19.16 (VCC), IC20.16 (VCC), IC21.8 (CS0), IC21.10 (CS1), IC21.12 (VCC), IC22.1 (VPP), IC22.28 (VCC), IC23.1 (VPP), IC23.27 (!PGM), IC23.28 (VCC), IC24.20 (VCC), IC24.22 (CS0), IC24.24 (CS1), IC25.20 (VCC), IC26.20 (VCC), IC27.4 (R), IC27.10 (R), IC27.14 (V+), IC28.6 (G1), IC28.16 (VCC), R1.2, R2.2, R3.2, R5.2, R6.2, R7.2, R8.2, R9.2, R12.2, R14.2, S2.A, S2.A1; also elsewhere on the board
VMA: IC17.5 (VMA), IC18.9 (I0)

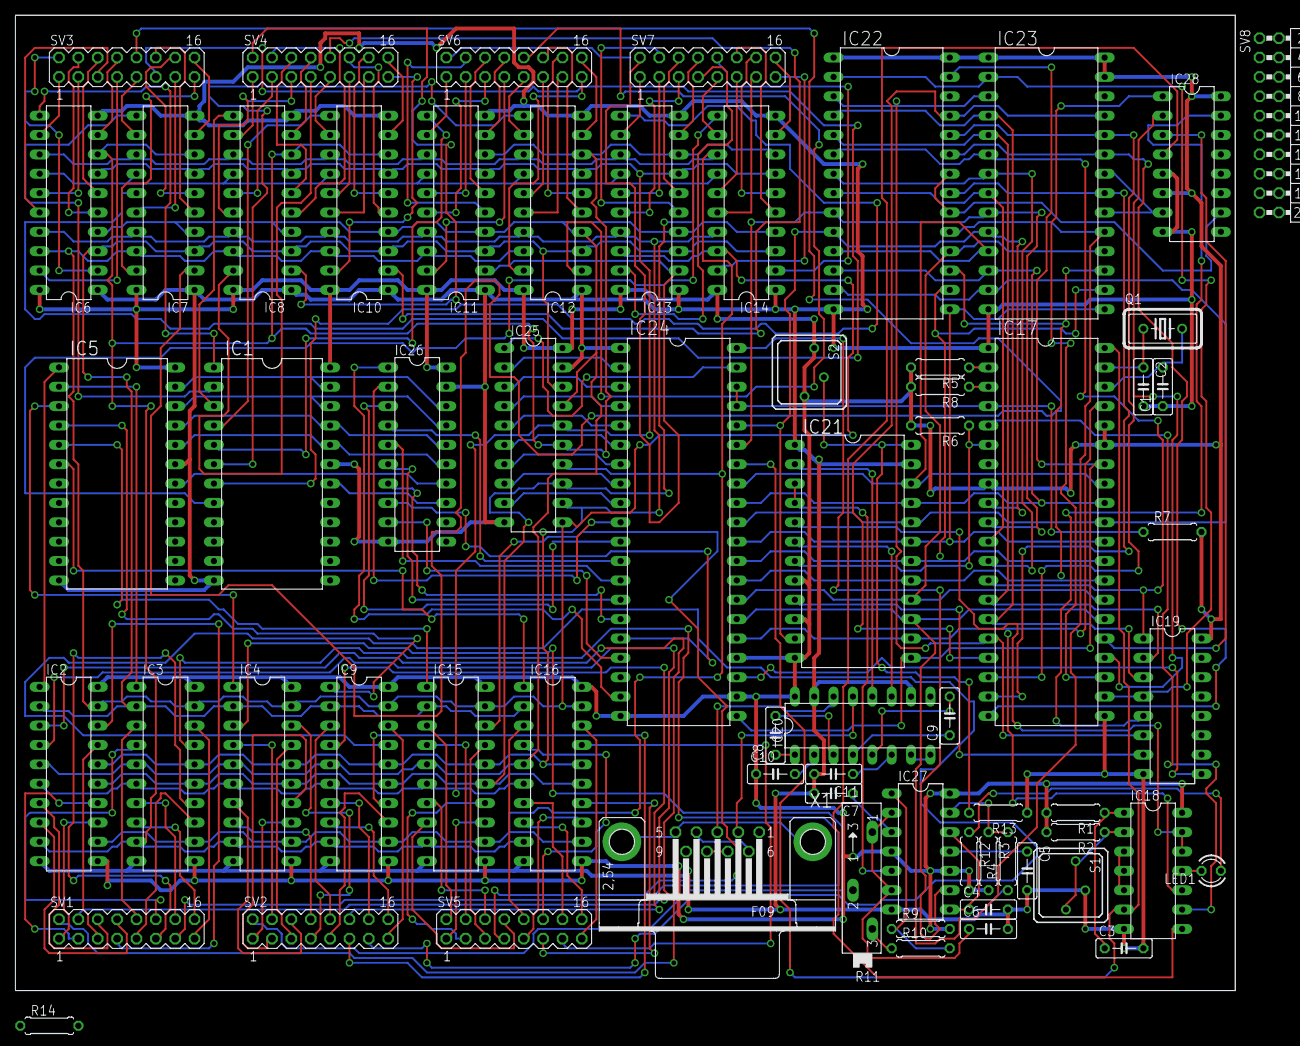
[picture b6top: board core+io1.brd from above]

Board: 2 copper layers, 160.0 x 127.9 mm, 66 parts (0 on the bottom side), 231 nets.
